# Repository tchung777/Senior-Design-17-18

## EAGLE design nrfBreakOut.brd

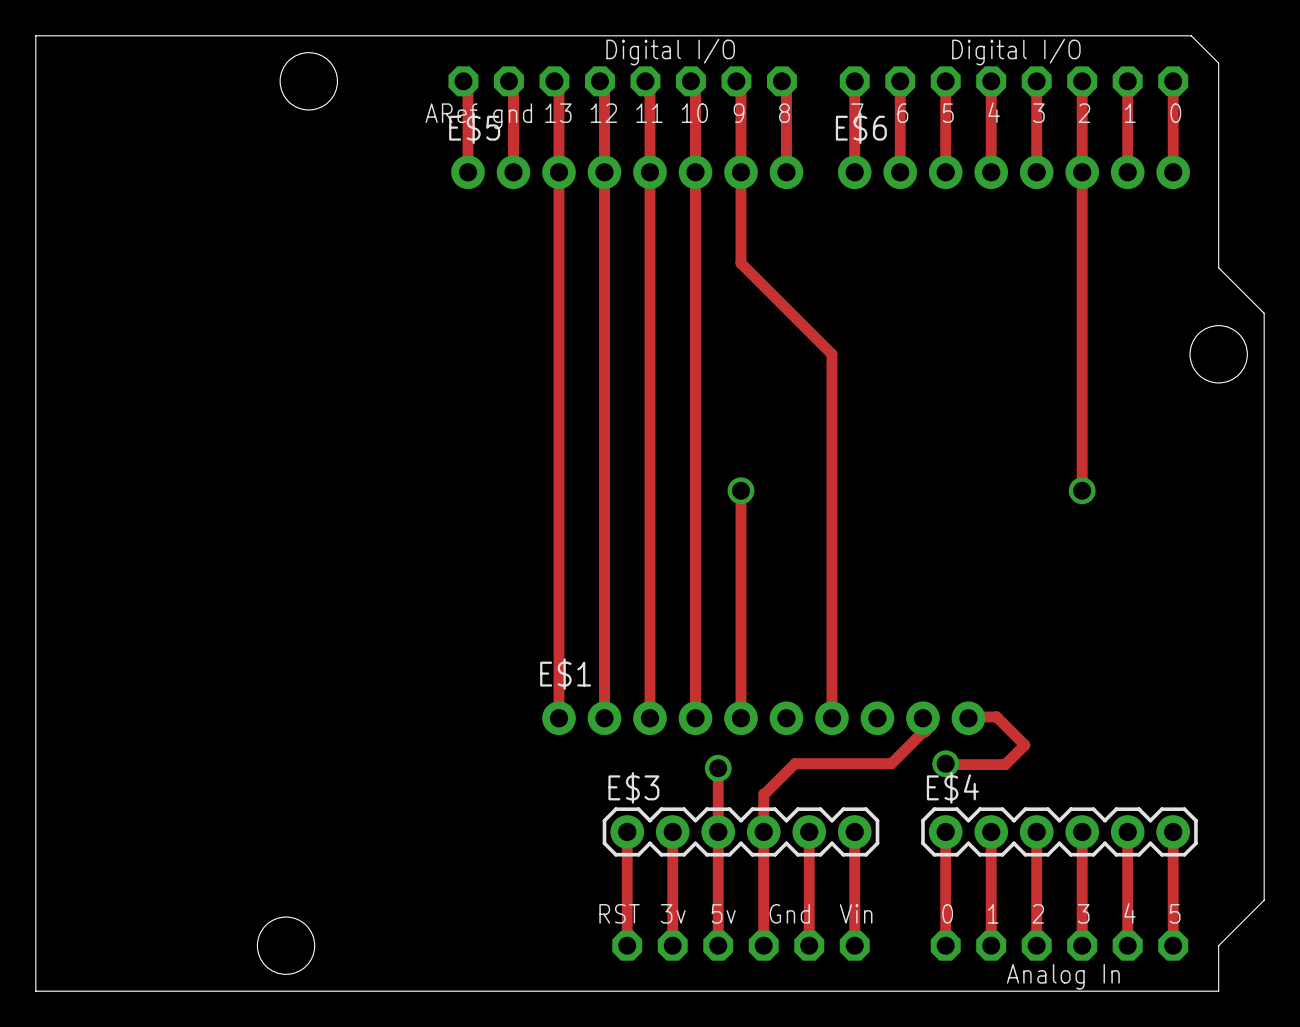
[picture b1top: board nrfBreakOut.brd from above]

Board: 2 copper layers, 68.6 x 53.3 mm, 6 parts (0 on the bottom side), 21 nets.

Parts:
E$1: 1X10_NO_SILK
E$2: ARDUINO
E$3, E$4: 1X06
E$5, E$6: 1X08_NO_SILK

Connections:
S$9: E$2.D7, E$6.1
S$10: E$2.D6, E$6.2
S$11: E$2.D5, E$6.3
S$12: E$2.D4, E$6.4
S$13: E$2.D3, E$6.5
S$14: E$2.D2, E$6.6
S$15: E$2.D1, E$6.7
S$16: E$2.D0, E$6.8
S$17: E$1.7, E$5.7
S$19: E$2.RESET, E$3.1
S$20: E$2.3V, E$3.2
S$21: E$2.5V, E$3.3
S$23: E$2.GND1, E$3.5
S$24: E$2.VIN, E$3.6
S$25: E$2.A0, E$4.1
S$26: E$2.A1, E$4.2
S$27: E$2.A2, E$4.3
S$28: E$2.A3, E$4.4
S$29: E$2.A4, E$4.5
S$30: E$2.A5, E$4.6
S$31: E$2.GND2, E$3.4

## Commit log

2017-12-17 Added files to prototype with SVM algorithm.
2018-02-02 Added MCU board.
2018-02-02 add line
2018-02-02 Added a line to MCU board.
2018-02-02 add another line
2018-02-02 Redid schematic for MCU; cleaned up wires by replacing with busses.
2018-02-02 Added decoupling capacitors to VCC.
2018-02-03 Moved schematic file to MCU_Related folder.
2018-02-03 Got rid of all the .s## files and moved them to MCU_Related.

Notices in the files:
parts and their libraries:
SparkFun-Connectors: Licensing: Creative Commons ShareAlike 4.0 International - https://creativecommons.org/licenses/by-sa/4.0
